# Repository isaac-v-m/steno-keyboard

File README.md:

# Steno Keyboard

A 26-key phonetic steno keyboard: 10 keys per hand plus 6 thumb keys, an Arduino
Pro Micro, and a 128x32 I2C OLED.

## Contents

| Path | What it is |
|---|---|
| `Steno_Board/` | KiCad 10 project (schematic + PCB) |
| `Free_Coding_Project/steno_firmware/` | Pro Micro firmware (Arduino sketch) |
| `Free_Coding_Project/steno_interpreter.py` | Reads strokes over USB serial and decodes them to phonemes |

## Hardware

- Arduino Pro Micro (ATmega32U4, 5V/16MHz)
- 26 Cherry MX-compatible switches, 26 1N4148 diodes
- 0.91" 128x32 SSD1306 OLED module (I2C, address 0x3C), pins GND/VCC/SCL/SDA

Each hand has its own COL2ROW matrix wired only to its side of the Pro Micro:

| | Left hand (J1) | Right hand (J2) |
|---|---|---|
| Top row | r1 = D1 (TX) | r4 = D21 |
| Bottom row | r2 = D0 (RX) | r5 = D20 |
| Thumb row | r3 = D9 | r6 = D10 |
| Columns | c1-c5 = D4-D8 | c6-c10 = D19, D18, D15, D14, D16 |

OLED: SDA = D2, SCL = D3.

## Firmware

Requires the Adafruit SSD1306 and Adafruit GFX libraries. In the Arduino IDE,
select **Arduino Leonardo** and upload `steno_firmware.ino`.

When all keys are released, the firmware sends one packet per stroke:

```
0xFF, keys0, keys1, keys2, keys3, flags
```

`keys0` = L00-L06, `keys1` = L07-L12, `keys2` = R00-R06, `keys3` = R07-R12
(bit n = nth key). Data bytes only use bits 0-6, so they never collide with the
0xFF start byte. `flags`: bit0 left layer, bit1 thumb layer, bit2 right layer.

## Interpreter

```
pip install -r Free_Coding_Project/requirements.txt
python Free_Coding_Project/steno_interpreter.py COM5
```

Pass the Pro Micro's COM port (defaults to COM3).

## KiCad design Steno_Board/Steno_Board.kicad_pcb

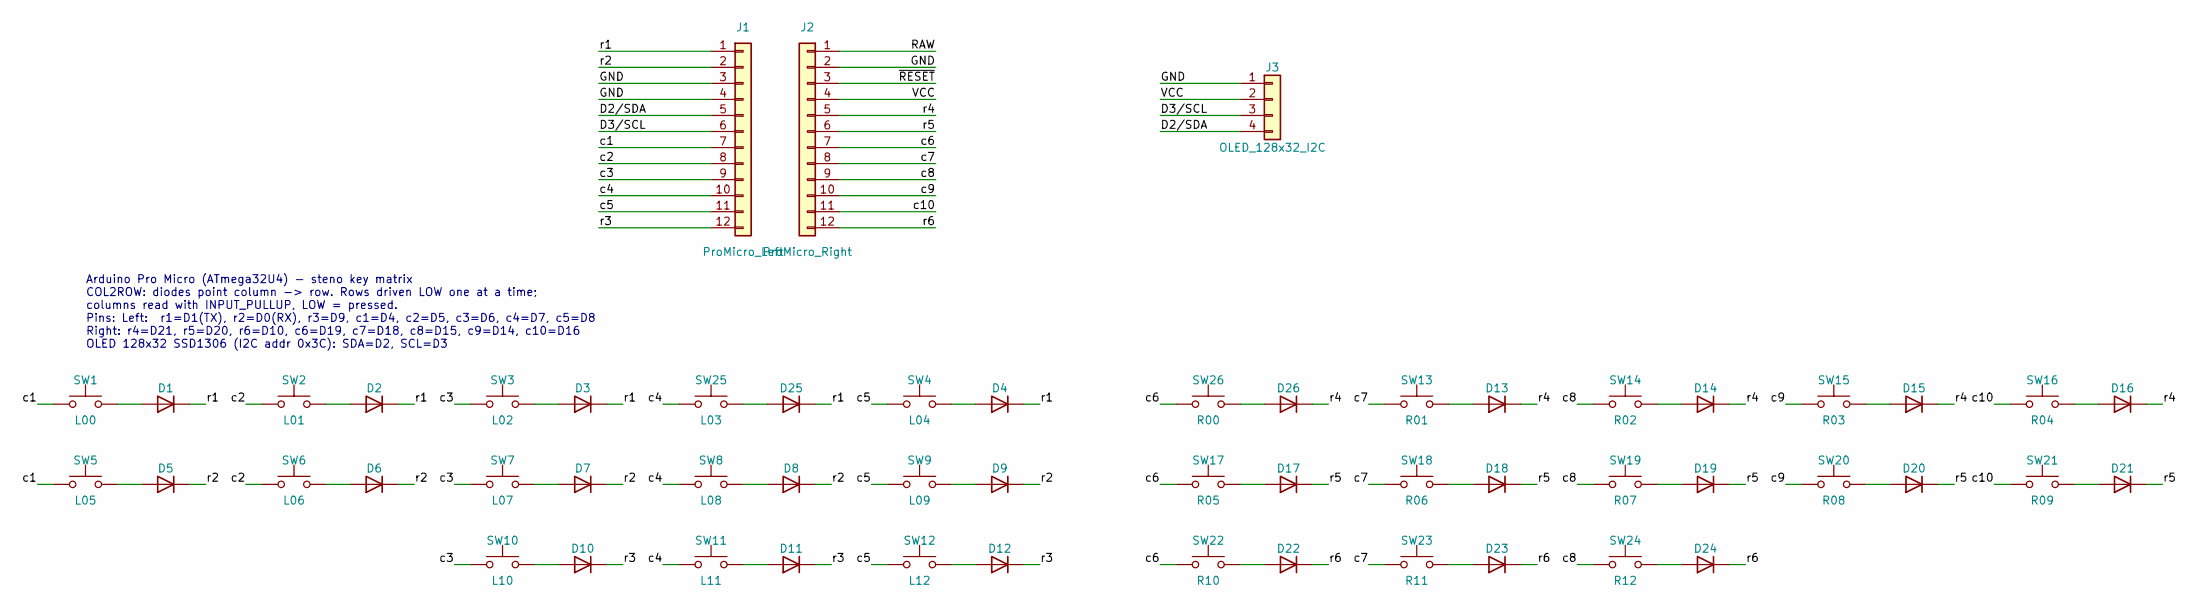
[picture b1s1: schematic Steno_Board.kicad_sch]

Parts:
D1, D2, D3, D4, D5, D6, D7, D8, D9, D10, D11, D12, D13, D14, D15, D16, D17, D18, D19, D20, D21, D22, D23, D24, D25, D26: 1N4148; D_DO-35_SOD27_P7.62mm_Horizontal
J1: ProMicro_Left; PinHeader_1x12_P2.54mm_Vertical
J2: ProMicro_Right; PinHeader_1x12_P2.54mm_Vertical
J3: OLED_128x32_I2C; PinHeader_1x04_P2.54mm_Vertical
SW1: L00; SW_Cherry_MX_1.00u_PCB
SW2: L01; SW_Cherry_MX_1.00u_PCB
SW3: L02; SW_Cherry_MX_1.00u_PCB
SW4: L04; SW_Cherry_MX_1.00u_PCB
SW5: L05; SW_Cherry_MX_1.00u_PCB
SW6: L06; SW_Cherry_MX_1.00u_PCB
SW7: L07; SW_Cherry_MX_1.00u_PCB
SW8: L08; SW_Cherry_MX_1.00u_PCB
SW9: L09; SW_Cherry_MX_1.00u_PCB
SW10: L10; SW_Cherry_MX_1.00u_PCB
SW11: L11; SW_Cherry_MX_1.00u_PCB
SW12: L12; SW_Cherry_MX_1.00u_PCB
SW13: R01; SW_Cherry_MX_1.00u_PCB
SW14: R02; SW_Cherry_MX_1.00u_PCB
SW15: R03; SW_Cherry_MX_1.00u_PCB
SW16: R04; SW_Cherry_MX_1.00u_PCB
SW17: R05; SW_Cherry_MX_1.00u_PCB
SW18: R06; SW_Cherry_MX_1.00u_PCB
SW19: R07; SW_Cherry_MX_1.00u_PCB
SW20: R08; SW_Cherry_MX_1.00u_PCB
SW21: R09; SW_Cherry_MX_1.00u_PCB
SW22: R10; SW_Cherry_MX_1.00u_PCB
SW23: R11; SW_Cherry_MX_1.00u_PCB
SW24: R12; SW_Cherry_MX_1.00u_PCB
SW25: L03; SW_Cherry_MX_1.00u_PCB
SW26: R00; SW_Cherry_MX_1.00u_PCB

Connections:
/D2/SDA: J1.5, J3.4
/D3/SCL: J1.6, J3.3
/GND: J1.3, J1.4, J2.2, J3.1
/RAW: J2.1
/VCC: J2.4, J3.2
/c1: J1.7, SW1.1, SW5.1
/c2: J1.8, SW2.1, SW6.1
/c3: J1.9, SW3.1, SW7.1, SW10.1
/c4: J1.10, SW8.1, SW11.1, SW25.1
/c5: J1.11, SW4.1, SW9.1, SW12.1
/c6: J2.7, SW17.1, SW22.1, SW26.1
/c7: J2.8, SW13.1, SW18.1, SW23.1
/c8: J2.9, SW14.1, SW19.1, SW24.1
/c9: J2.10, SW15.1, SW20.1
/c10: J2.11, SW16.1, SW21.1
/r1: D1.1 (K), D2.1 (K), D3.1 (K), D4.1 (K), D25.1 (K), J1.1
/r2: D5.1 (K), D6.1 (K), D7.1 (K), D8.1 (K), D9.1 (K), J1.2
/r3: D10.1 (K), D11.1 (K), D12.1 (K), J1.12
/r4: D13.1 (K), D14.1 (K), D15.1 (K), D16.1 (K), D26.1 (K), J2.5
/r5: D17.1 (K), D18.1 (K), D19.1 (K), D20.1 (K), D21.1 (K), J2.6
/r6: D22.1 (K), D23.1 (K), D24.1 (K), J2.12
/~RESET: J2.3
unnamed: D1.2 (A), SW1.2
unnamed: D2.2 (A), SW2.2
unnamed: D3.2 (A), SW3.2
unnamed: D4.2 (A), SW4.2
unnamed: D5.2 (A), SW5.2
unnamed: D6.2 (A), SW6.2
unnamed: D7.2 (A), SW7.2
unnamed: D8.2 (A), SW8.2
unnamed: D9.2 (A), SW9.2
unnamed: D10.2 (A), SW10.2
unnamed: D11.2 (A), SW11.2
unnamed: D12.2 (A), SW12.2
unnamed: D13.2 (A), SW13.2
unnamed: D14.2 (A), SW14.2
unnamed: D15.2 (A), SW15.2
unnamed: D16.2 (A), SW16.2
unnamed: D17.2 (A), SW17.2
unnamed: D18.2 (A), SW18.2
unnamed: D19.2 (A), SW19.2
unnamed: D20.2 (A), SW20.2
unnamed: D21.2 (A), SW21.2
unnamed: D22.2 (A), SW22.2
unnamed: D23.2 (A), SW23.2
unnamed: D24.2 (A), SW24.2
unnamed: D25.2 (A), SW25.2
unnamed: D26.2 (A), SW26.2

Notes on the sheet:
Arduino Pro Micro (ATmega32U4) - steno key matrix COL2ROW: diodes point column -> row. Rows driven LOW one at a time; columns read with INPUT_PULLUP, LOW = pressed. Pins: Left: r1=D1(TX), r2=D0(RX), r3=D9, c1=D4, c2=D5, c3=D6, c4=D7, c5=D8 Right: r4=D21, r5=D20, r6=D10, c6=D19, c7=D18, c8=D15, c9=D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

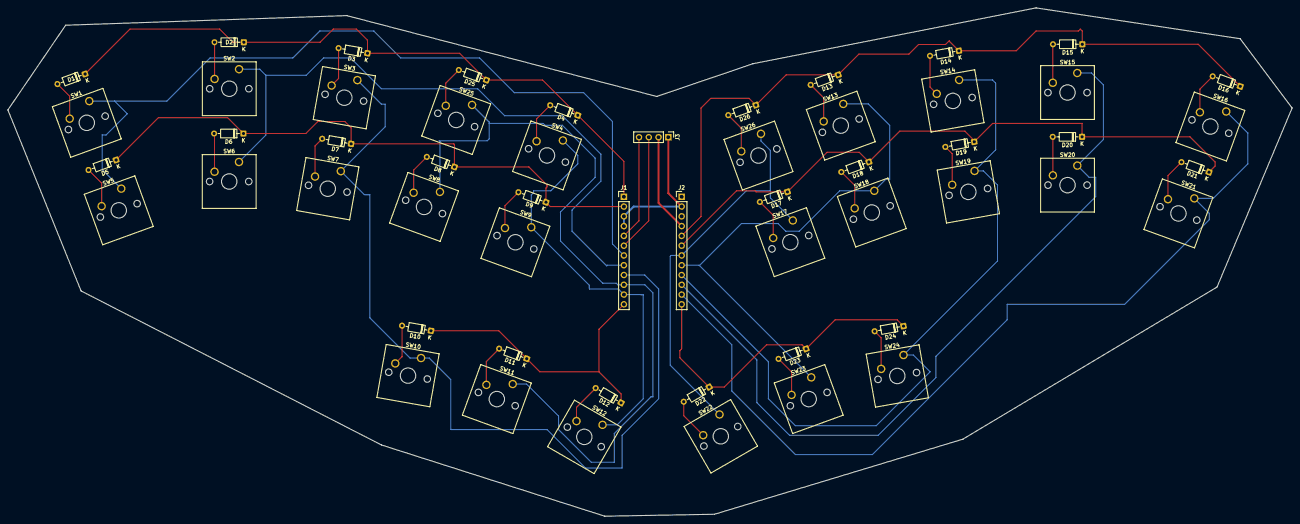
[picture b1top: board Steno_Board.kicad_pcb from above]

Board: 2 copper layers, 333.5 x 132.0 mm, 55 parts (0 on the bottom side), 46 nets.
